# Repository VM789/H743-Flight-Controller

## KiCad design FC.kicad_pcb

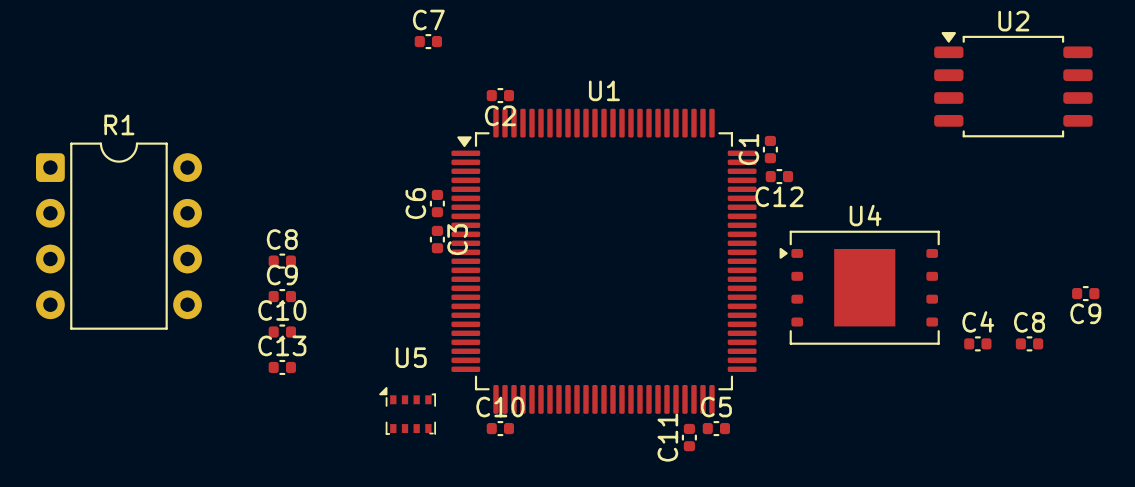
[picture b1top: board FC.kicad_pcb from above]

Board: 2 copper layers, 21 parts (0 on the bottom side), 7 nets, no tracks yet.

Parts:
C1, C2, C3, C4, C5, C6, C8, C9, C9#2, C10, C13: 100n; C_0402_1005Metric
C7: 4u7; C_0402_1005Metric
C8#2, C10#2: 1u; C_0402_1005Metric
C11, C12: 2u2; C_0402_1005Metric
R1: 0; DIP-8_W7.62mm
U1: STM32H743VITx; LQFP-100_14x14mm_P0.5mm
U2: W25Q128JVS; SOIC-8_5.3x5.3mm_P1.27mm
U4: W25Q128JVE; WSON-8-1EP_8x6mm_P1.27mm_EP3.4x4.3mm
U5: BMP280; Bosch_LGA-8_2x2.5mm_P0.65mm_ClockwisePinNumbering

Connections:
/H743/vcap1: C11.2, U1.48 (VCAP)
/H743/vcap2: C12.2, U1.73 (VCAP)
GND: C1.1, C2.1, C3.1, C4.1, C5.1, C6.1, C7.1, C8.1, C8#2.2, C9.1, C9#2.2, C10.1, C10#2.2, C11.1, C12.1, C13.2, U1.10 (VSS), U1.19 (VSSA), U1.26 (VSS), U1.49 (VSS), U1.74 (VSS), U1.99 (VSS)
VDDA: C10#2.1, C13.1, R1.1, U1.21 (VDDA)
VERF+: C8#2.1, C9#2.1, R1.2, U1.20 (VREF+)
VREF: C8.2, C9.2
vdd_mcu: C1.2, C2.2, C3.2, C4.2, C5.2, C6.2, C7.2, U1.6 (VBAT), U1.11 (VDD), U1.27 (VDD), U1.50 (VDD), U1.75 (VDD), U1.100 (VDD)
